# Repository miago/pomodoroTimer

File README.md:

pomodoroTimer
=============

my own pomodoro timer with a optical notification system

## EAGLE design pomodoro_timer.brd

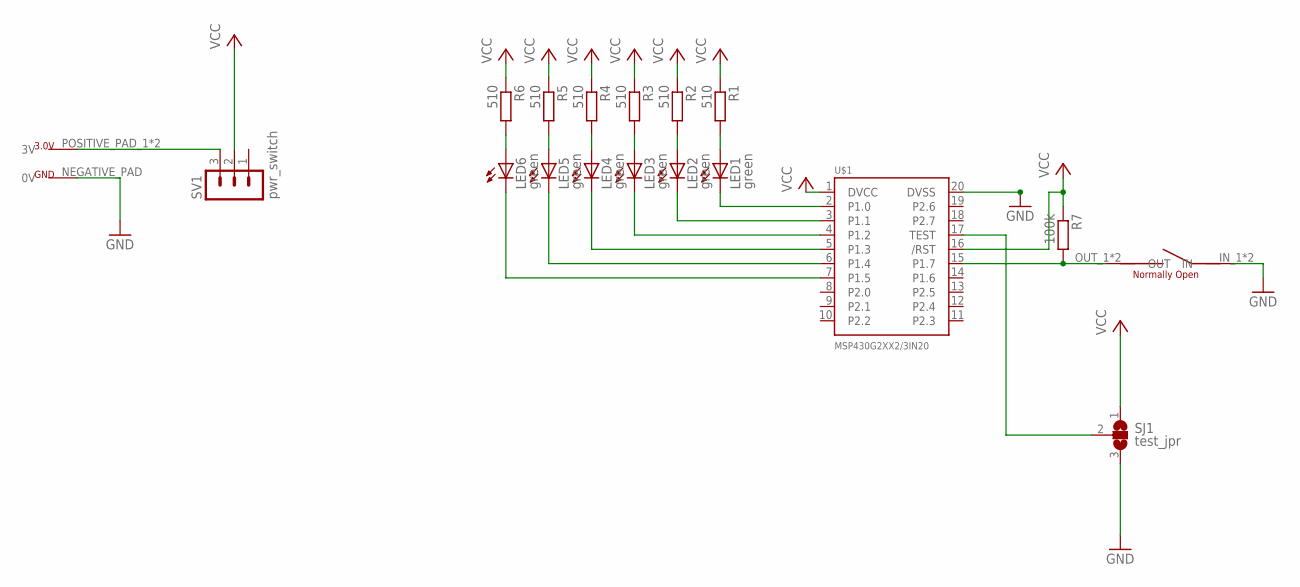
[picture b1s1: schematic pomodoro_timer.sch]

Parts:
LED1, LED2, LED3, LED4, LED5, LED6: green; LED_1206
R1, R2, R3, R4, R5, R6: 510; M1206
R7: 100k; M1206
SJ1: test_jpr; SJ_2
SV1: pwr_switch; MA03-1
U$1: MSP430G2XX2/3IN20; DIL20
U$2: CR2032_HOLDERNORMAL; CR2032_HOLDER
U$3: SWITCH_SIMPLENORMAL; SWITCH_SIMPLE

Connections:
GND: SJ1.3, U$1.20 (DVSS), U$2.NEGATIVE_PAD (0V), U$3.IN_1 (IN), U$3.IN_2 (IN)
unnamed: LED1.C, U$1.2 (P1.0)
unnamed: LED1.A, R1.2
unnamed: LED2.A, R2.2
unnamed: LED3.A, R3.2
unnamed: LED4.A, R4.2
unnamed: LED5.A, R5.2
unnamed: LED6.A, R6.2
unnamed: LED2.C, U$1.3 (P1.1)
unnamed: LED3.C, U$1.4 (P1.2)
unnamed: LED4.C, U$1.5 (P1.3)
unnamed: LED5.C, U$1.6 (P1.4)
unnamed: LED6.C, U$1.7 (P1.5)
unnamed: R7.2, U$1.15 (P1.7), U$3.OUT_1 (OUT), U$3.OUT_2 (OUT)
unnamed: SJ1.2, U$1.17 (TEST)
POS_BAT: SV1.3, U$2.POSITIVE_PAD_1 (3V), U$2.POSITIVE_PAD_2 (3V)
VCC: R1.1, R2.1, R3.1, R4.1, R5.1, R6.1, R7.1, SJ1.1, SV1.2, U$1.1 (DVCC), U$1.16 (/RST)

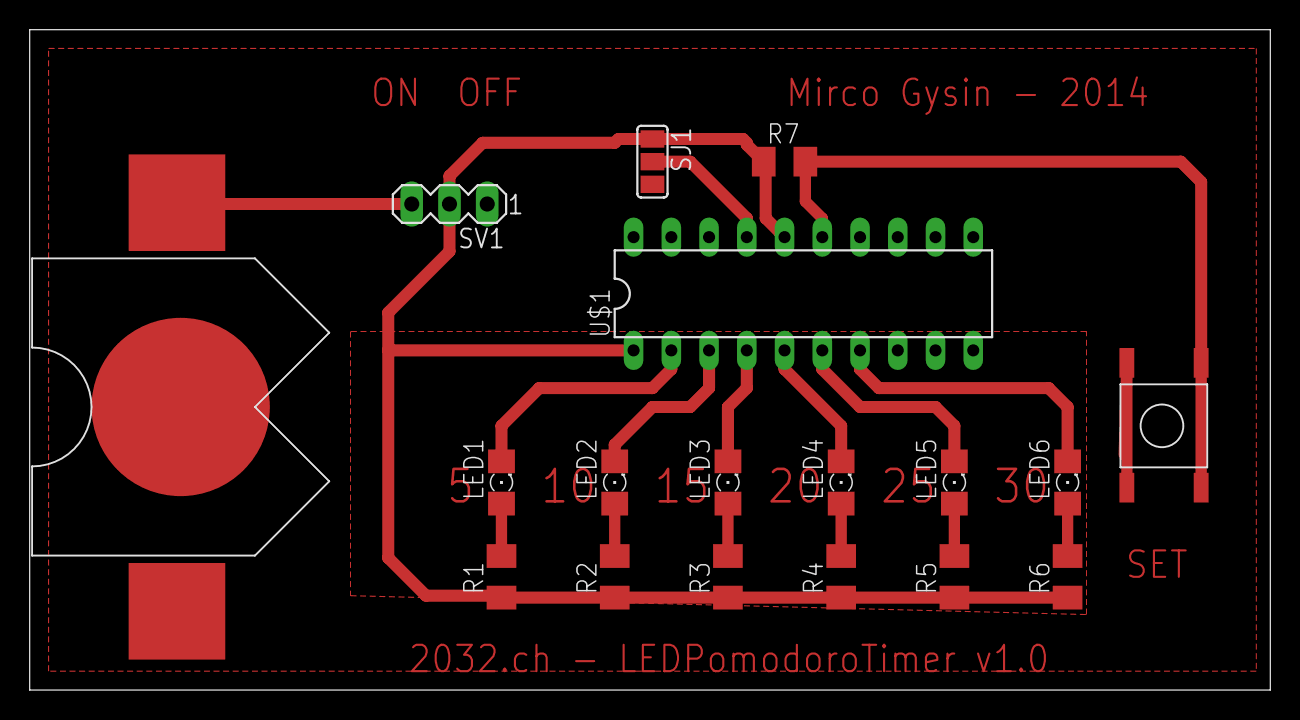
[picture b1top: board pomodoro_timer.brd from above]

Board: 2 copper layers, 83.5 x 44.4 mm, 18 parts (0 on the bottom side), 17 nets.

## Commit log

2014-12-07 initial release
2014-12-07 added 5 minutes labels
2014-12-08 added ground plane + jumper for test input
2014-12-10 working timer, not proud of it
